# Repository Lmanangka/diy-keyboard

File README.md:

# diy-keyboard

Making and design my own keyboard from scratch

## Design and Components

### Front View Components

- Switch Cherry MX
- Cherry MX Stabilizer(PCB mount stabs)

### Back View Components

- Diode 1N4148W

### MCU View Components

- U2 MCU ATmega32U4-AU
- Y1 Crystal oscilator 16MHz
- SW69 Reset Switch SKQG
- C1-C2 Capacitor 22pF
- C3-C7 Capacitor 0.1uF
- C8 Capacitor 10uF
- R3, R6 Resistor 10K Ohm
- R4-R5 Resistor 22 Ohm
- J1 AVR-ISP Connector

### USB-Type-C View Components

- USB Type C
- FB1 Ferrite Bead
- R1-R2 Resistor 5.1K Ohm
- F1 PTC Fuse 500mA
- U1 PRTR5V0U2X

## Footprints Source

- [Switch and stabilizer](https://github.com/perigoso/keyswitch-kicad-library)
- [USB Type C](https://github.com/ai03-2725/Type-C.pretty)

## References And Credit

- [Designing a keyboard from scratch](https://www.masterzen.fr/2020/05/03/designing-a-keyboard-part-1)(mostly I used this as guide)
- [PCB Designer Guide](https://wiki.ai03.com/books/pcb-design/chapter/pcb-designer-guide)(starting point)
- [keyboard-pcb-guide](https://github.com/ruiqimao/keyboard-pcb-guide)(for reference)

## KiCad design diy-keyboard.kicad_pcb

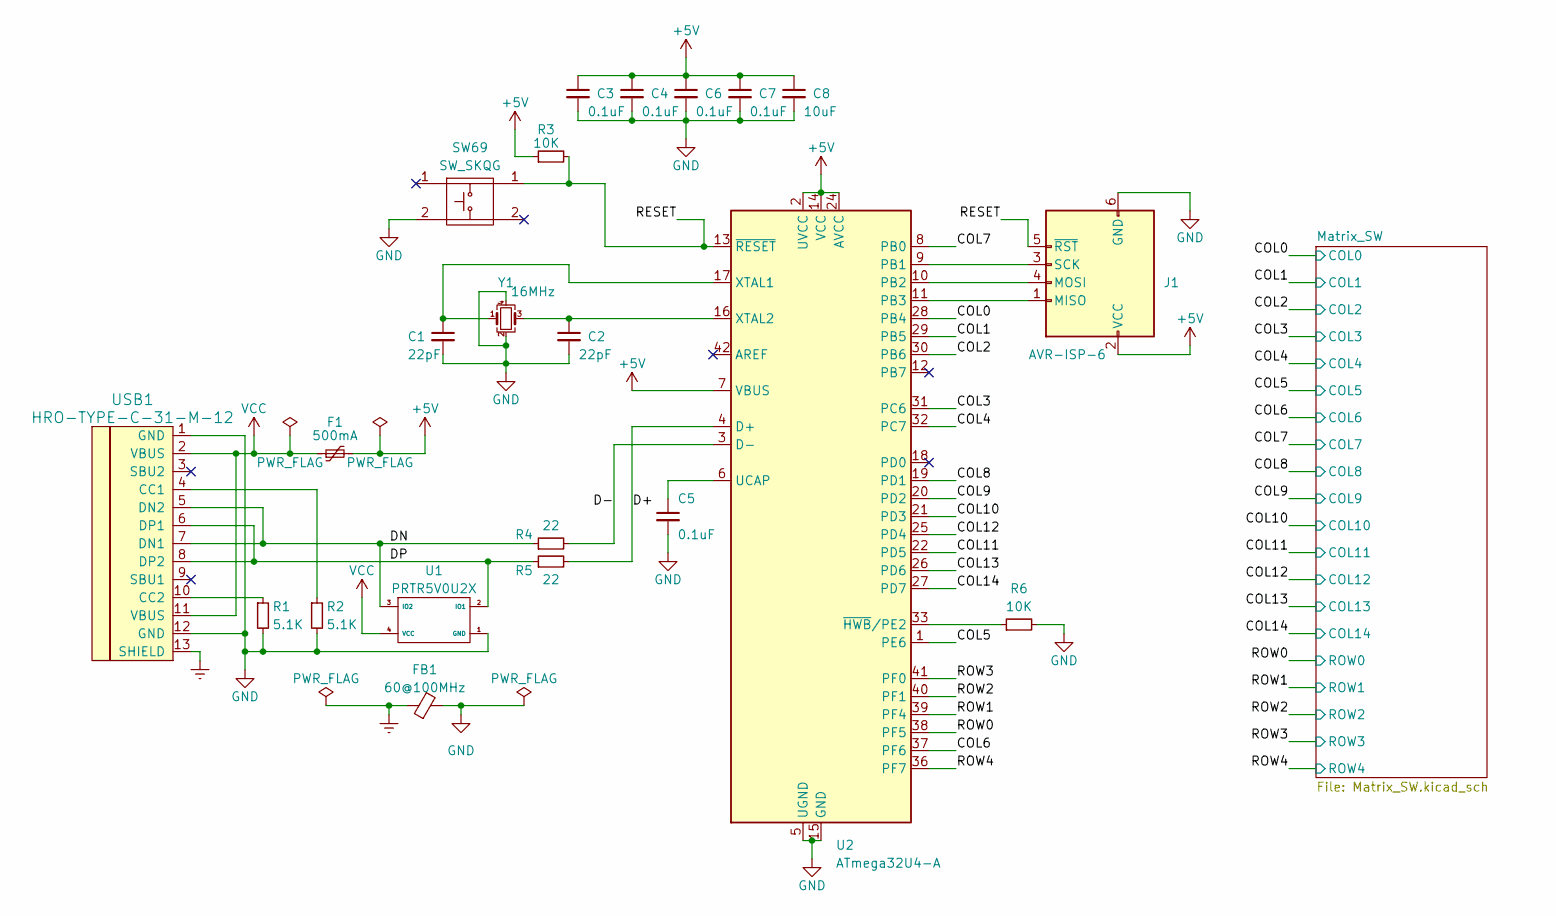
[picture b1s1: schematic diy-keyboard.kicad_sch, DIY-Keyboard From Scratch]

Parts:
C1, C2: 22pF; C_0805_2012Metric_Pad1.18x1.45mm_HandSolder
C3, C4, C5, C6, C7: 0.1uF; C_0805_2012Metric_Pad1.18x1.45mm_HandSolder
C8: 10uF; C_0805_2012Metric_Pad1.18x1.45mm_HandSolder
F1: 500mA; Fuse_1206_3216Metric_Pad1.42x1.75mm_HandSolder
FB1: 60@100MHz; L_0805_2012Metric_Pad1.15x1.40mm_HandSolder
J1: AVR-ISP-6; Reset_Pretty-Mask
R1, R2: 5.1K; R_0805_2012Metric_Pad1.20x1.40mm_HandSolder
R3, R6: 10K; R_0805_2012Metric_Pad1.20x1.40mm_HandSolder
R4, R5: 22; R_0805_2012Metric_Pad1.20x1.40mm_HandSolder
SW69: SW_SKQG; SW_SPST_SKQG_WithStem
U1: PRTR5V0U2X; SOT-143
U2: ATmega32U4-A; TQFP-44_10x10mm_P0.8mm
USB1: HRO-TYPE-C-31-M-12; HRO-TYPE-C-31-M-12-HandSoldering
Y1: 16MHz; Crystal_SMD_3225-4Pin_3.2x2.5mm_HandSoldering

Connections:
+5V: C3.1, C4.1, C6.1, C7.1, C8.1, F1.2, J1.2 (VCC), R3.1, U2.2 (UVCC), U2.7 (VBUS), U2.14 (VCC), U2.24 (AVCC), U2.34 (VCC), U2.44 (AVCC)
/COL0: U2.28 (PB4); also elsewhere on the board
/COL1: U2.29 (PB5); also elsewhere on the board
/COL2: U2.30 (PB6); also elsewhere on the board
/COL3: U2.31 (PC6); also elsewhere on the board
/COL4: U2.32 (PC7); also elsewhere on the board
/COL5: U2.1 (PE6); also elsewhere on the board
/COL6: U2.37 (PF6); also elsewhere on the board
/COL7: U2.8 (PB0); also elsewhere on the board
/COL8: U2.19 (PD1); also elsewhere on the board
/COL9: U2.20 (PD2); also elsewhere on the board
/COL10: U2.21 (PD3); also elsewhere on the board
/COL11: U2.22 (PD5); also elsewhere on the board
/COL12: U2.25 (PD4); also elsewhere on the board
/COL13: U2.26 (PD6); also elsewhere on the board
/COL14: U2.27 (PD7); also elsewhere on the board
/D+: R5.2, U2.4 (D+)
/D-: R4.2, U2.3 (D-)
/DN: R4.1, U1.3 (IO2), USB1.5 (DN2), USB1.7 (DN1)
/DP: R5.1, U1.2 (IO1), USB1.6 (DP1), USB1.8 (DP2)
/RESET: J1.5 (~RST), R3.2, SW69.1, U2.13 (~RESET)
/ROW0: U2.38 (PF5); also elsewhere on the board
/ROW1: U2.39 (PF4); also elsewhere on the board
/ROW2: U2.40 (PF1); also elsewhere on the board
/ROW3: U2.41 (PF0); also elsewhere on the board
/ROW4: U2.36 (PF7); also elsewhere on the board
Earth: FB1.1, USB1.13 (SHIELD)
GND: C1.2, C2.2, C3.2, C4.2, C5.2, C6.2, C7.2, C8.2, FB1.2, J1.6 (GND), R1.2, R2.2, R6.2, SW69.2, U1.1 (GND), U2.5 (UGND), U2.15 (GND), U2.23 (GND), U2.35 (GND), U2.43 (GND), USB1.1 (GND), USB1.12 (GND), Y1.2, Y1.4
unnamed: J1.1 (MISO), U2.11 (PB3)
unnamed: J1.4 (MOSI), U2.10 (PB2)
unnamed: J1.3 (SCK), U2.9 (PB1)
unnamed: C5.1, U2.6 (UCAP)
unnamed: C1.1, U2.17 (XTAL1), Y1.1
unnamed: C2.1, U2.16 (XTAL2), Y1.3
unnamed: R6.1, U2.33 (~HWB/PE2)
unnamed: R2.1, USB1.4 (CC1)
unnamed: R1.1, USB1.10 (CC2)
VCC: F1.1, U1.4 (VCC), USB1.2 (VBUS), USB1.11 (VBUS)

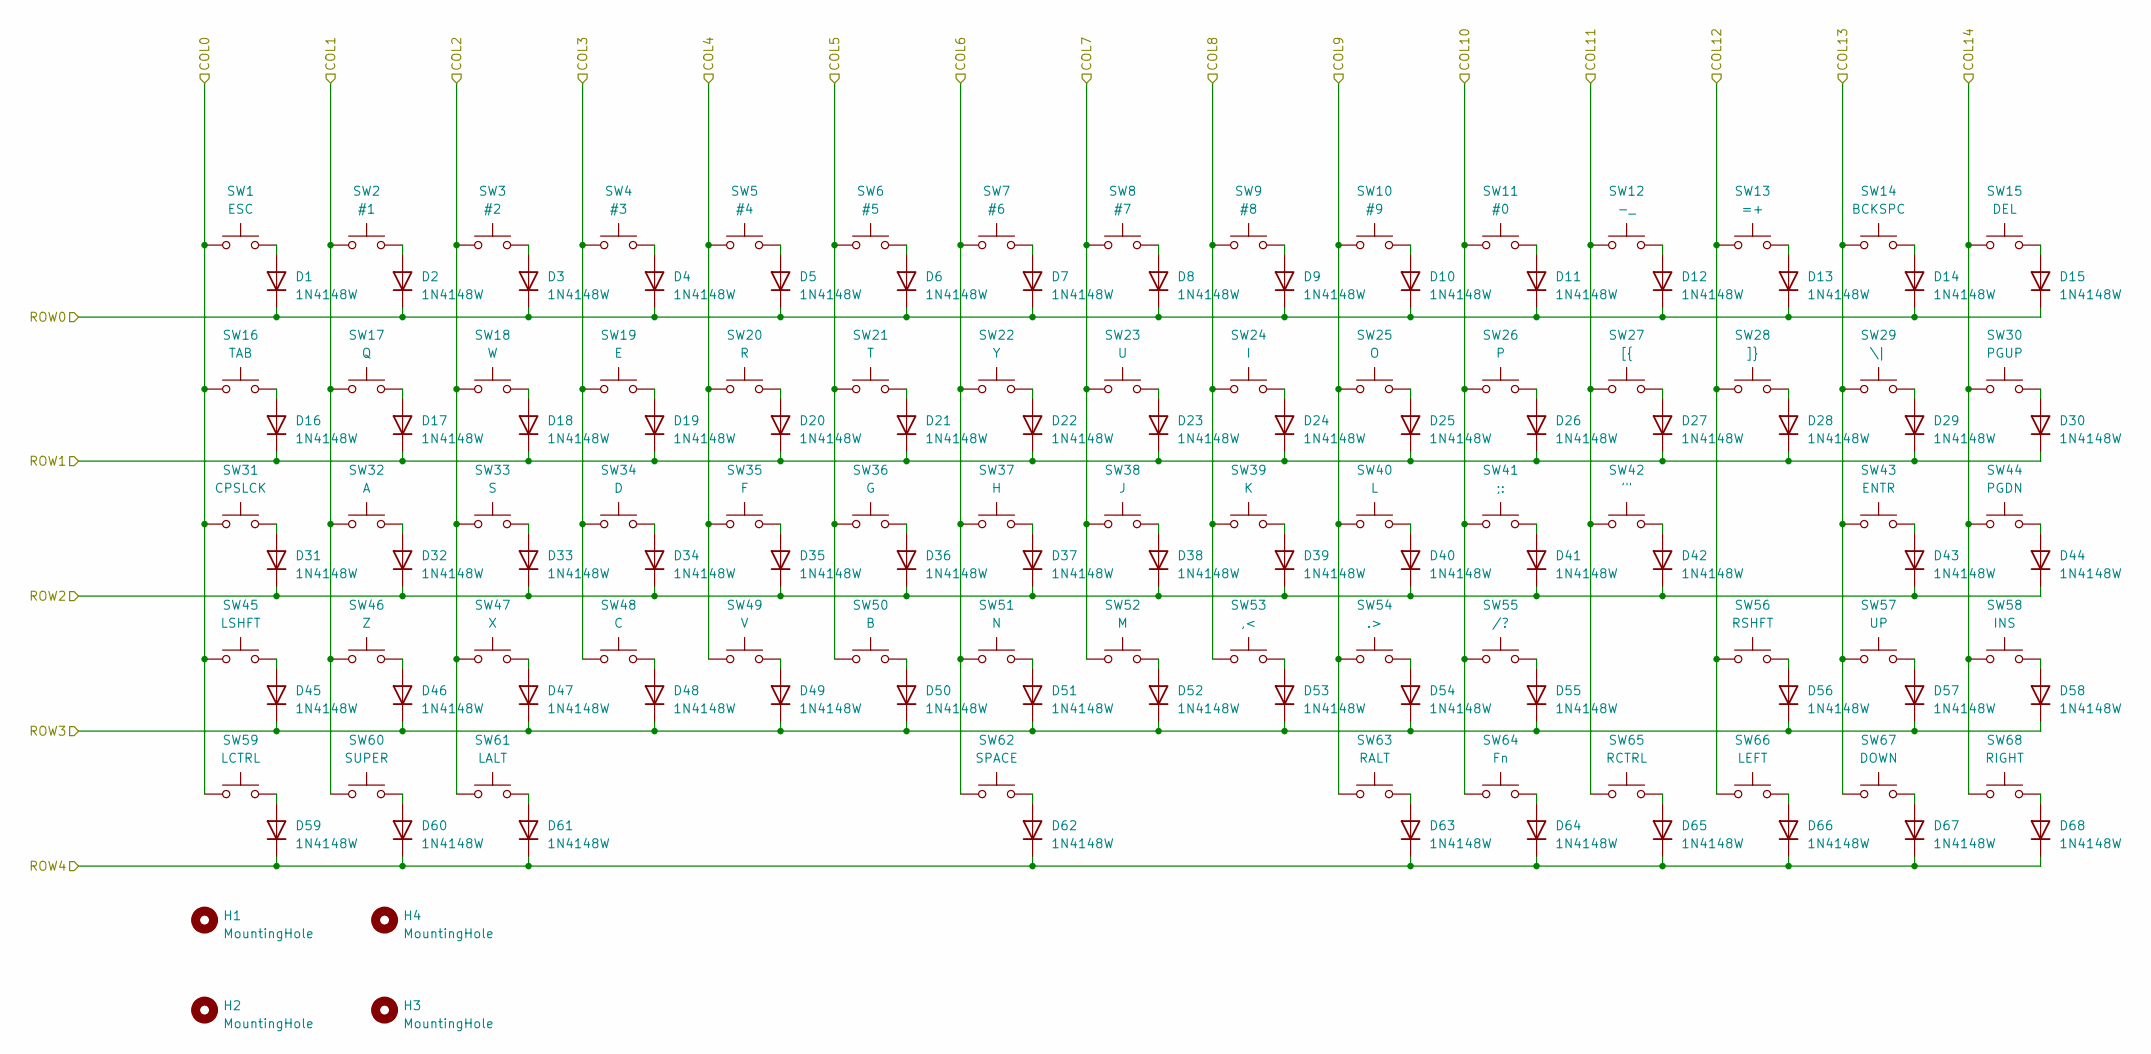
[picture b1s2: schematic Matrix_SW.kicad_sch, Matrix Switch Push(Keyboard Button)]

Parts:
D1, D2, D3, D4, D5, D6, D7, D8, D9, D10, D11, D12, D13, D14, D15, D16, D17, D18, D19, D20, D21, D22, D23, D24, D25, D26, D27, D28, D29, D30, D31, D32, D33, D34, D35, D36, D37, D38, D39, D40, D41, D42, D43, D44, D45, D46, D47, D48, D49, D50, D51, D52, D53, D54, D55, D56, D57, D58, D59, D60, D61, D62, D63, D64, D65, D66, D67, D68: 1N4148W; D_SOD-123
H1: MountingHole; Stabilizer_Cherry_MX_6.25u
H2, H3, H4: MountingHole; Stabilizer_Cherry_MX_2.00u
SW1: ESC; SW_Cherry_MX_PCB_1.00u
SW2: #1; SW_Cherry_MX_PCB_1.00u
SW3: #2; SW_Cherry_MX_PCB_1.00u
SW4: #3; SW_Cherry_MX_PCB_1.00u
SW5: #4; SW_Cherry_MX_PCB_1.00u
SW6: #5; SW_Cherry_MX_PCB_1.00u
SW7: #6; SW_Cherry_MX_PCB_1.00u
SW8: #7; SW_Cherry_MX_PCB_1.00u
SW9: #8; SW_Cherry_MX_PCB_1.00u
SW10: #9; SW_Cherry_MX_PCB_1.00u
SW11: #0; SW_Cherry_MX_PCB_1.00u
SW12: -_; SW_Cherry_MX_PCB_1.00u
SW13: =+; SW_Cherry_MX_PCB_1.00u
SW14: BCKSPC; SW_Cherry_MX_PCB_2.00u
SW15: DEL; SW_Cherry_MX_PCB_1.00u
SW16: TAB; SW_Cherry_MX_PCB_1.50u
SW17: Q; SW_Cherry_MX_PCB_1.00u
SW18: W; SW_Cherry_MX_PCB_1.00u
SW19: E; SW_Cherry_MX_PCB_1.00u
SW20: R; SW_Cherry_MX_PCB_1.00u
SW21: T; SW_Cherry_MX_PCB_1.00u
SW22: Y; SW_Cherry_MX_PCB_1.00u
SW23: U; SW_Cherry_MX_PCB_1.00u
SW24: I; SW_Cherry_MX_PCB_1.00u
SW25: O; SW_Cherry_MX_PCB_1.00u
SW26: P; SW_Cherry_MX_PCB_1.00u
SW27: [{; SW_Cherry_MX_PCB_1.00u
SW28: ]}; SW_Cherry_MX_PCB_1.00u
SW29: \|; SW_Cherry_MX_PCB_1.50u
SW30: PGUP; SW_Cherry_MX_PCB_1.00u
SW31: CPSLCK; SW_Cherry_MX_PCB_1.75u
SW32: A; SW_Cherry_MX_PCB_1.00u
SW33: S; SW_Cherry_MX_PCB_1.00u
SW34: D; SW_Cherry_MX_PCB_1.00u
SW35: F; SW_Cherry_MX_PCB_1.00u
SW36: G; SW_Cherry_MX_PCB_1.00u
SW37: H; SW_Cherry_MX_PCB_1.00u
SW38: J; SW_Cherry_MX_PCB_1.00u
SW39: K; SW_Cherry_MX_PCB_1.00u
SW40: L; SW_Cherry_MX_PCB_1.00u
SW41: ;:; SW_Cherry_MX_PCB_1.00u
SW42: '"; SW_Cherry_MX_PCB_1.00u
SW43: ENTR; SW_Cherry_MX_PCB_2.25u
SW44: PGDN; SW_Cherry_MX_PCB_1.00u
SW45: LSHFT; SW_Cherry_MX_PCB_2.25u
SW46: Z; SW_Cherry_MX_PCB_1.00u
SW47: X; SW_Cherry_MX_PCB_1.00u
SW48: C; SW_Cherry_MX_PCB_1.00u
SW49: V; SW_Cherry_MX_PCB_1.00u
SW50: B; SW_Cherry_MX_PCB_1.00u
SW51: N; SW_Cherry_MX_PCB_1.00u
SW52: M; SW_Cherry_MX_PCB_1.00u
SW53: ,<; SW_Cherry_MX_PCB_1.00u
SW54: .>; SW_Cherry_MX_PCB_1.00u
SW55: /?; SW_Cherry_MX_PCB_1.00u
SW56: RSHFT; SW_Cherry_MX_PCB_1.75u
SW57: UP; SW_Cherry_MX_PCB_1.00u
SW58: INS; SW_Cherry_MX_PCB_1.00u
SW59: LCTRL; SW_Cherry_MX_PCB_1.50u
SW60: SUPER; SW_Cherry_MX_PCB_1.00u
SW61: LALT; SW_Cherry_MX_PCB_1.00u
SW62: SPACE; SW_Cherry_MX_PCB_6.50u
SW63: RALT; SW_Cherry_MX_PCB_1.00u
SW64: Fn; SW_Cherry_MX_PCB_1.00u
SW65: RCTRL; SW_Cherry_MX_PCB_1.00u
SW66: LEFT; SW_Cherry_MX_PCB_1.00u
SW67: DOWN; SW_Cherry_MX_PCB_1.00u
SW68: RIGHT; SW_Cherry_MX_PCB_1.00u

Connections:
/COL0: SW1.1, SW16.1, SW31.1, SW45.1, SW59.1; also elsewhere on the board
/COL1: SW2.1, SW17.1, SW32.1, SW46.1, SW60.1; also elsewhere on the board
/COL2: SW3.1, SW18.1, SW33.1, SW47.1, SW61.1; also elsewhere on the board
/COL3: SW4.1, SW19.1, SW34.1, SW48.1; also elsewhere on the board
/COL4: SW5.1, SW20.1, SW35.1, SW49.1; also elsewhere on the board
/COL5: SW6.1, SW21.1, SW36.1, SW50.1; also elsewhere on the board
/COL6: SW7.1, SW22.1, SW37.1, SW51.1, SW62.1; also elsewhere on the board
/COL7: SW8.1, SW23.1, SW38.1, SW52.1; also elsewhere on the board
/COL8: SW9.1, SW24.1, SW39.1, SW53.1; also elsewhere on the board
/COL9: SW10.1, SW25.1, SW40.1, SW54.1, SW63.1; also elsewhere on the board
/COL10: SW11.1, SW26.1, SW41.1, SW55.1, SW64.1; also elsewhere on the board
/COL11: SW12.1, SW27.1, SW42.1, SW65.1; also elsewhere on the board
/COL12: SW13.1, SW28.1, SW56.1, SW66.1; also elsewhere on the board
/COL13: SW14.1, SW29.1, SW43.1, SW57.1, SW67.1; also elsewhere on the board
/COL14: SW15.1, SW30.1, SW44.1, SW58.1, SW68.1; also elsewhere on the board
/ROW0: D1.1 (K), D2.1 (K), D3.1 (K), D4.1 (K), D5.1 (K), D6.1 (K), D7.1 (K), D8.1 (K), D9.1 (K), D10.1 (K), D11.1 (K), D12.1 (K), D13.1 (K), D14.1 (K), D15.1 (K); also elsewhere on the board
/ROW1: D16.1 (K), D17.1 (K), D18.1 (K), D19.1 (K), D20.1 (K), D21.1 (K), D22.1 (K), D23.1 (K), D24.1 (K), D25.1 (K), D26.1 (K), D27.1 (K), D28.1 (K), D29.1 (K), D30.1 (K); also elsewhere on the board
/ROW2: D31.1 (K), D32.1 (K), D33.1 (K), D34.1 (K), D35.1 (K), D36.1 (K), D37.1 (K), D38.1 (K), D39.1 (K), D40.1 (K), D41.1 (K), D42.1 (K), D43.1 (K), D44.1 (K); also elsewhere on the board
/ROW3: D45.1 (K), D46.1 (K), D47.1 (K), D48.1 (K), D49.1 (K), D50.1 (K), D51.1 (K), D52.1 (K), D53.1 (K), D54.1 (K), D55.1 (K), D56.1 (K), D57.1 (K), D58.1 (K); also elsewhere on the board
/ROW4: D59.1 (K), D60.1 (K), D61.1 (K), D62.1 (K), D63.1 (K), D64.1 (K), D65.1 (K), D66.1 (K), D67.1 (K), D68.1 (K); also elsewhere on the board
unnamed: D1.2 (A), SW1.2
unnamed: D2.2 (A), SW2.2
unnamed: D3.2 (A), SW3.2
unnamed: D4.2 (A), SW4.2
unnamed: D5.2 (A), SW5.2
unnamed: D6.2 (A), SW6.2
unnamed: D7.2 (A), SW7.2
unnamed: D8.2 (A), SW8.2
unnamed: D9.2 (A), SW9.2
unnamed: D10.2 (A), SW10.2
unnamed: D11.2 (A), SW11.2
unnamed: D12.2 (A), SW12.2
unnamed: D13.2 (A), SW13.2
unnamed: D14.2 (A), SW14.2
unnamed: D15.2 (A), SW15.2
unnamed: D16.2 (A), SW16.2
unnamed: D17.2 (A), SW17.2
unnamed: D18.2 (A), SW18.2
unnamed: D19.2 (A), SW19.2
unnamed: D20.2 (A), SW20.2
unnamed: D21.2 (A), SW21.2
unnamed: D22.2 (A), SW22.2
unnamed: D23.2 (A), SW23.2
unnamed: D24.2 (A), SW24.2
unnamed: D25.2 (A), SW25.2
unnamed: D26.2 (A), SW26.2
unnamed: D27.2 (A), SW27.2
unnamed: D28.2 (A), SW28.2
unnamed: D29.2 (A), SW29.2
unnamed: D30.2 (A), SW30.2
unnamed: D31.2 (A), SW31.2
unnamed: D32.2 (A), SW32.2
unnamed: D33.2 (A), SW33.2
unnamed: D34.2 (A), SW34.2
unnamed: D35.2 (A), SW35.2
unnamed: D36.2 (A), SW36.2
unnamed: D37.2 (A), SW37.2
unnamed: D38.2 (A), SW38.2
unnamed: D39.2 (A), SW39.2
unnamed: D40.2 (A), SW40.2
unnamed: D41.2 (A), SW41.2
unnamed: D42.2 (A), SW42.2
unnamed: D43.2 (A), SW43.2
unnamed: D44.2 (A), SW44.2
unnamed: D45.2 (A), SW45.2
unnamed: D46.2 (A), SW46.2
unnamed: D47.2 (A), SW47.2
unnamed: D48.2 (A), SW48.2
unnamed: D49.2 (A), SW49.2
unnamed: D50.2 (A), SW50.2
unnamed: D51.2 (A), SW51.2
unnamed: D52.2 (A), SW52.2
unnamed: D53.2 (A), SW53.2
unnamed: D54.2 (A), SW54.2
unnamed: D55.2 (A), SW55.2
unnamed: D56.2 (A), SW56.2
unnamed: D57.2 (A), SW57.2
unnamed: D58.2 (A), SW58.2
unnamed: D59.2 (A), SW59.2
unnamed: D60.2 (A), SW60.2
unnamed: D61.2 (A), SW61.2
unnamed: D62.2 (A), SW62.2
unnamed: D63.2 (A), SW63.2
unnamed: D64.2 (A), SW64.2
unnamed: D65.2 (A), SW65.2
unnamed: D66.2 (A), SW66.2
unnamed: D67.2 (A), SW67.2
unnamed: D68.2 (A), SW68.2

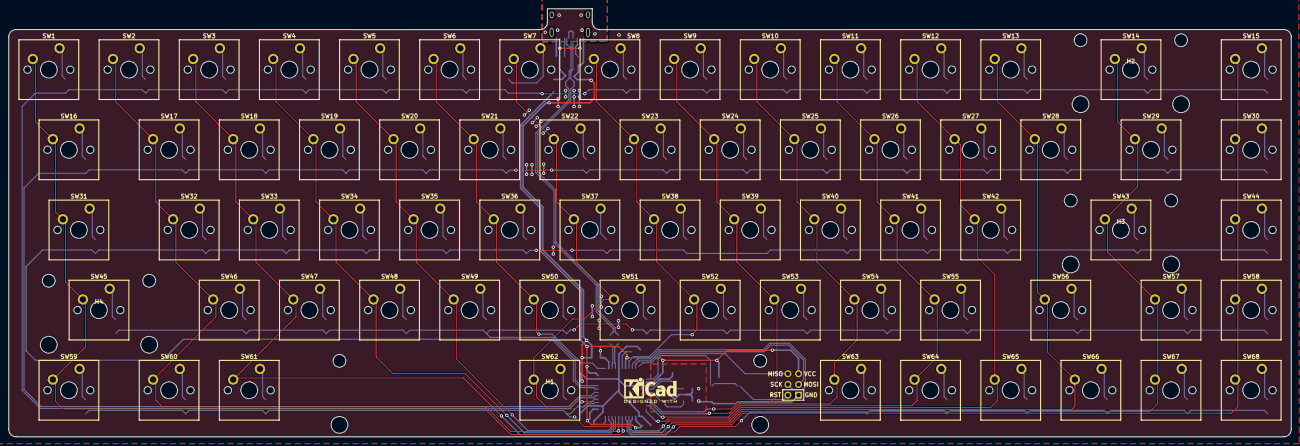
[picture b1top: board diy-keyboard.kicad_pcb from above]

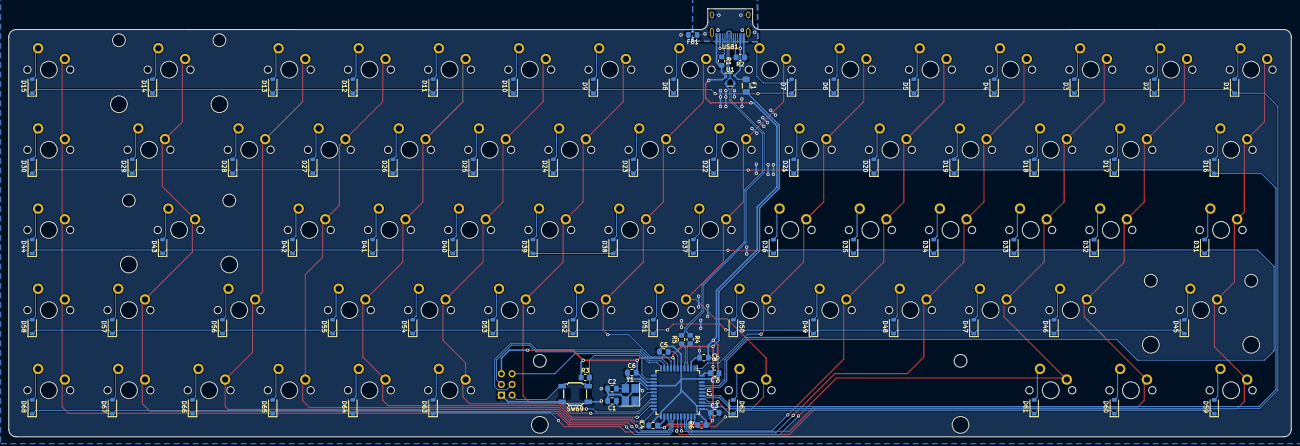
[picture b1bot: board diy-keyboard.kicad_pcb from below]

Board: 2 copper layers, 304.8 x 101.7 mm, 162 parts (89 on the bottom side), 106 nets.

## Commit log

2023-03-07 add kicad files
2023-03-07 Create LICENSE
2023-03-07 Add submodules
2023-03-07 Add .gitignore
2023-03-07 Add diy-keyboard.kicad_prl to .gitignore
2023-03-07 Add footprint libraries
2023-03-07 Add fp-info-cache to .gitignore
2023-03-08 Remove submodule
2023-03-08 Add submodule Type-C.pretty to local_lib
2023-03-08 Add Cherry MX and Mounting keyboard stabilizer footprint
2023-03-08 Add button SW_SKQG library
2023-03-08 Add ESD protection PRTR5V0U2X footprint
2023-03-08 Add keyboard button matrix schematic
2023-03-08 Update Library and schematic
2023-03-08 Update schematic connecting matrix keyboard switch to MCU
2023-03-08 Add new ISP-header library
2023-03-08 Assigning footprint to components
2023-03-08 Add ISP-header library
2023-03-09 Change keyboard layout and reasign keyboard footprints
2023-03-09 Add directory for SW-SK library
2023-03-09 Making edge cuts PCB taking a shape
2023-03-10 Routing switch and diode
2023-03-10 Add label for diferential pair
2023-03-10 Routing USB and Crystal Oscillator
2023-03-10 Reassign footprint SW59 and re-allign keyboard layout
2023-03-12 Change Diode to more specific type 1N4148 SOD-123
2023-03-12 Change diode footprint to 1N4148 SOD-123 and re-routing PCB
2023-03-12 Re-organize local library
2023-03-12 Re-organize local symbol library
2023-03-12 Re-organize local footprint library
2023-03-12 Re-assign symbol and footprint to match local library
2023-03-12 Adding ferrite bead to usb sield
2023-03-12 Routing usb shield to ferrite bead
2023-03-12 Add img for documentation
2023-03-14 Add kicad logo
2023-03-14 Add image
2023-03-14 Update image
